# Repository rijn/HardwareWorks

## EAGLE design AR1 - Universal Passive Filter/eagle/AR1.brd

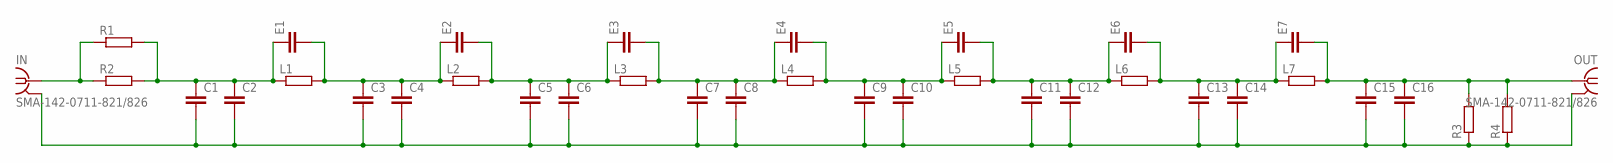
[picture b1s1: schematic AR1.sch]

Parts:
C1, C2, C3, C4, C5, C6, C7, C8, C9, C10, C11, C12, C13, C14, C15, C16: C; C0805
E1, E2, E3, E4, E5, E6, E7: C; C0805
IN: SMA-142-0711-821/826; J502-ND-142-0711-821/826
L1, L2, L3, L4, L5, L6, L7: R; R0805
OUT: SMA-142-0711-821/826; J502-ND-142-0711-821/826
R1, R2, R3, R4: R; R0805

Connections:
GND: C1.2, C2.2, C3.2, C4.2, C5.2, C6.2, C7.2, C8.2, C9.2, C10.2, C11.2, C12.2, C13.2, C14.2, C15.2, C16.2, IN.G@1 (2), IN.G@2 (2), IN.G@3 (2), IN.G@4 (2), OUT.G@1 (2), OUT.G@2 (2), OUT.G@3 (2), OUT.G@4 (2), R3.1, R4.1
unnamed: C1.1, C2.1, E1.1, L1.1, R1.2, R2.2
unnamed: IN.1, R1.1, R2.1
unnamed: C15.1, C16.1, E7.2, L7.2, OUT.1, R3.2, R4.2
unnamed: C3.1, C4.1, E1.2, E2.1, L1.2, L2.1
unnamed: C5.1, C6.1, E2.2, E3.1, L2.2, L3.1
unnamed: C7.1, C8.1, E3.2, E4.1, L3.2, L4.1
unnamed: C9.1, C10.1, E4.2, E5.1, L4.2, L5.1
unnamed: C11.1, C12.1, E5.2, E6.1, L5.2, L6.1
unnamed: C13.1, C14.1, E6.2, E7.1, L6.2, L7.1

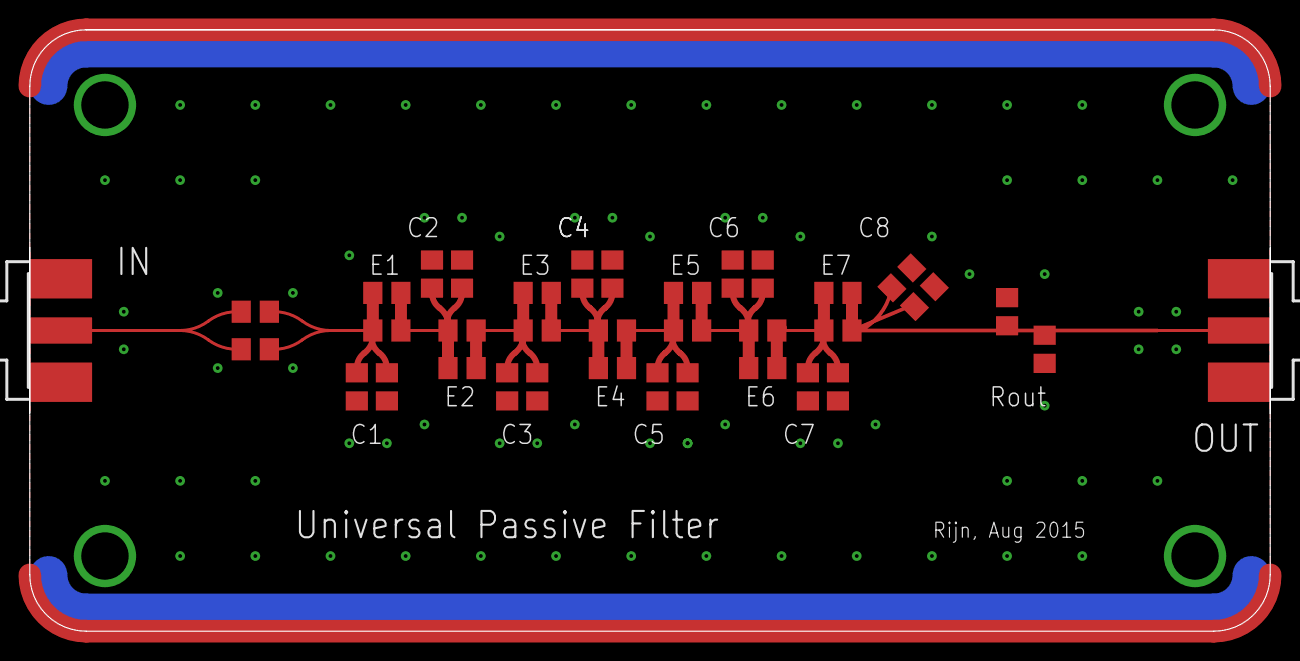
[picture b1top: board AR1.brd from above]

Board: 2 copper layers, 83.8 x 40.6 mm, 36 parts (0 on the bottom side), 10 nets.

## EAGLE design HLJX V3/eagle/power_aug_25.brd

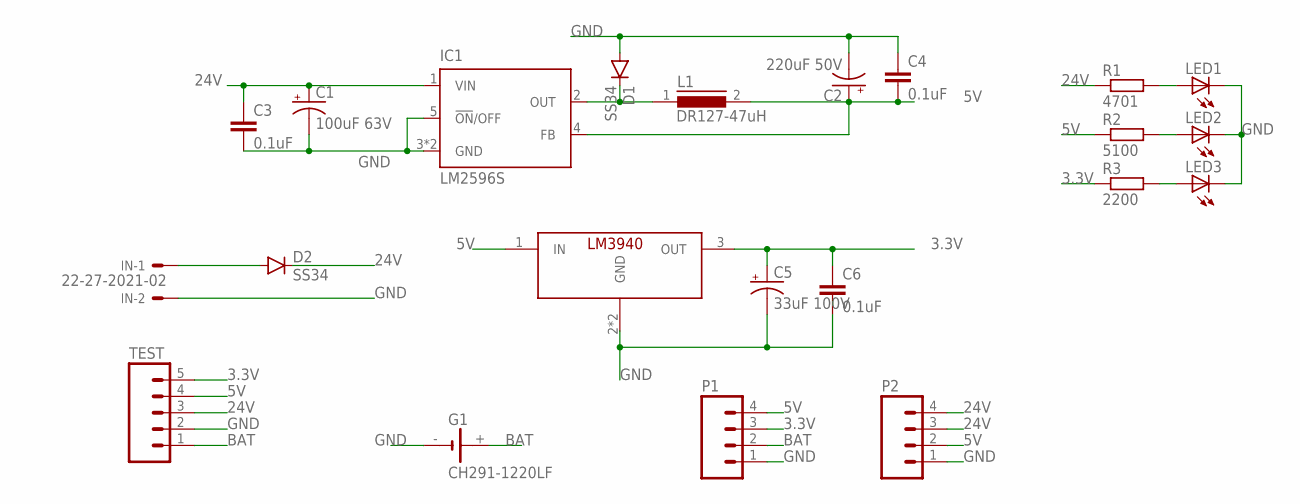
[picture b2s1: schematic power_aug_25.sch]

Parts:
C1: 100uF 63V; NIC_10X10.5_CAP
C2: 220uF 50V; NIC_10X10.5_CAP
C3, C4, C6: 0.1uF; 0603-CAP
C5: 33uF 100V; NIC_10X10.5_CAP
D1, D2: SS34; SMA-DIODE_ALT
G1: CH291-1220LF
IC1: LM2596S; TO263-5
IN: 22-27-2021-02; 6410-02
L1: DR127-47uH; DR127
LED1, LED2, LED3: LEDCHIPLED_0805; CHIPLED_0805
P1, P2: M04SMD2; 1X04-1MM-RA
R1: 4701; R0603
R2: 5100; R0603
R3: 2200; R0603
TEST: M05LOCK_LONGPADS; 1X05_LOCK_LONGPADS
U$1: LM3940; SOT223

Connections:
3.3V: C5.+, C6.1, P1.3, R3.1, TEST.5, U$1.3 (OUT)
5V: C2.+, C4.2, IC1.4 (FB), L1.2, P1.4, P2.2, R2.1, TEST.4, U$1.1 (IN)
24V: C1.+, C3.1, D2.C, IC1.1 (VIN), P2.3, P2.4, R1.1, TEST.3
BAT: G1.+, P1.2, TEST.1
GND: C1.-, C2.-, C3.2, C4.1, C5.-, C6.2, D1.A, G1.-, IC1.3 (GND), IC1.5 (!ON!/OFF), IC1.6 (GND), IN.2, LED1.C, LED2.C, LED3.C, P1.1, P2.1, TEST.2, U$1.2 (GND), U$1.4 (GND)
unnamed: D2.A, IN.1
unnamed: D1.C, IC1.2 (OUT), L1.1
unnamed: LED1.A, R1.2
unnamed: LED2.A, R2.2
unnamed: LED3.A, R3.2

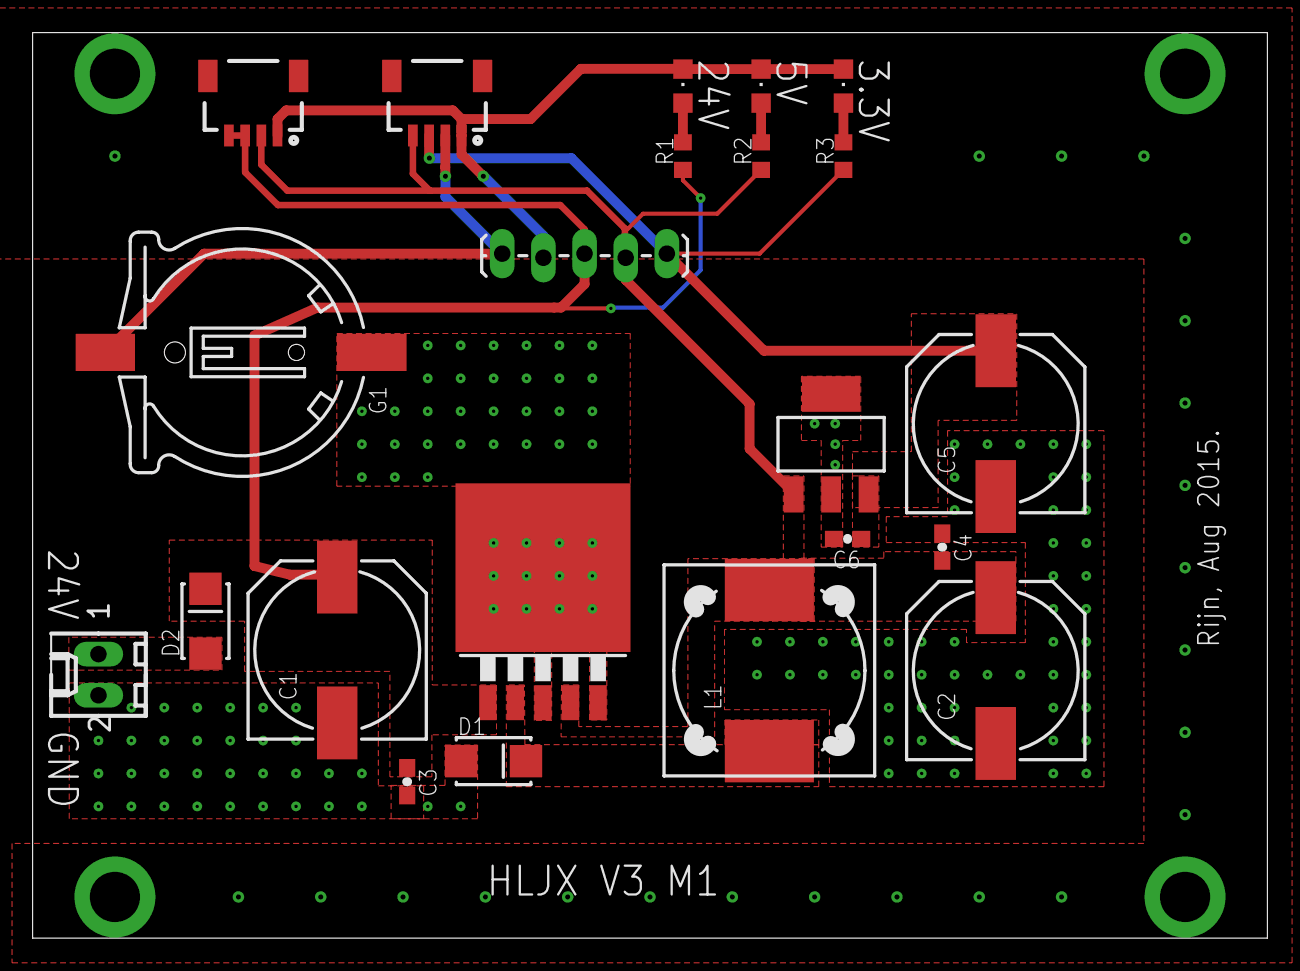
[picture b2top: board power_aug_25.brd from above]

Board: 2 copper layers, 76.2 x 55.9 mm, 22 parts (0 on the bottom side), 10 nets.

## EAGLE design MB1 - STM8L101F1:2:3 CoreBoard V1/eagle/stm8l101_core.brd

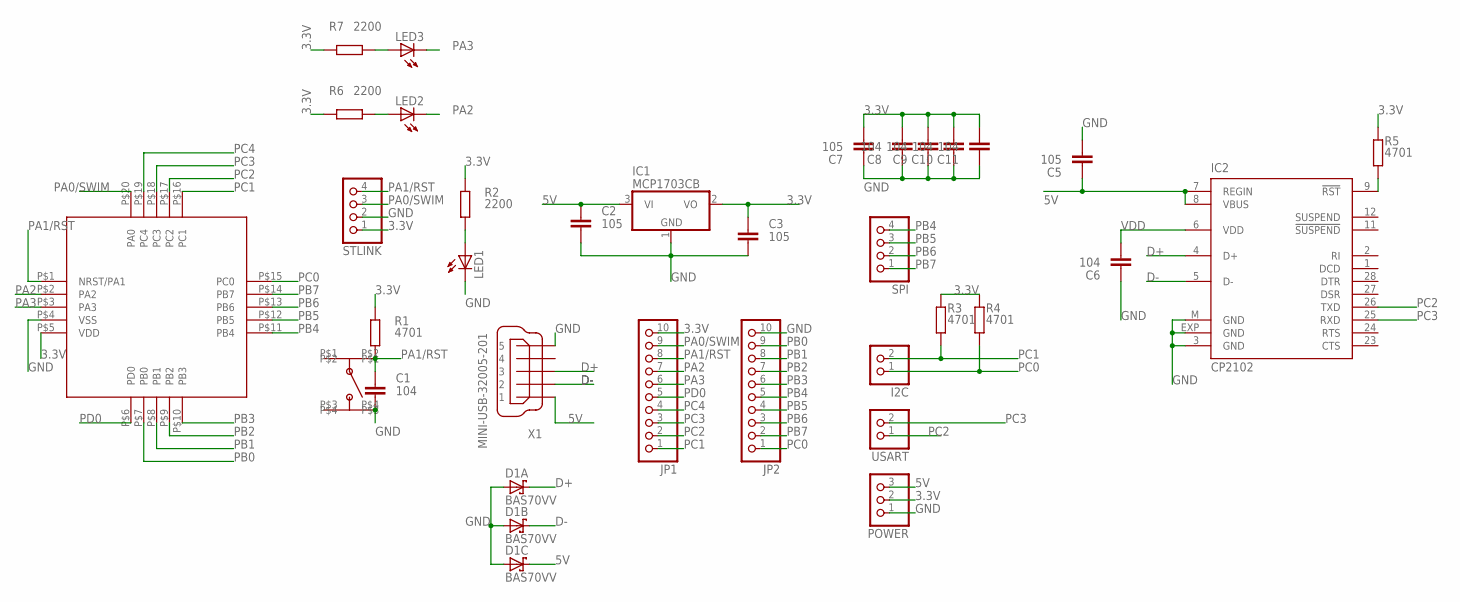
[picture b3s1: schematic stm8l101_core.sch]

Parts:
C1, C6, C8, C9, C10, C11: 104; C0603
C2, C3, C5, C7: 105; C0603
D1: BAS70VV; SOT666
I2C: PINHD-1X2; 1X02
IC1: MCP1703CB; SOT23
IC2: CP2102; MLP28
JP1, JP2: PINHD-1X10; 1X10
LED1, LED2, LED3: LED_ESML0603; LED_SML0603
POWER: PINHD-1X3; 1X03
R1, R3, R4, R5: 4701; R0603
R2, R6, R7: 2200; R0603
SPI: PINHD-1X4; 1X04
STLINK: PINHD-1X4; 1X04
U$1: STM8L101; UFQFPN20
U$2: KFC-A05; SWITCH-4X4
USART: PINHD-1X2; 1X02
X1: MINI-USB-32005-201; 32005-201

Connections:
3.3V: C3.1, C7.2, C8.2, C9.2, C10.2, C11.2, IC1.2 (VO), JP1.10, POWER.2, R1.1, R2.1, R3.1, R4.1, R5.1, R6.1, R7.1, STLINK.1, U$1.P$5 (VDD)
5V: C2.1, C5.1, D1.4 (C), IC1.3 (VI), IC2.7 (REGIN), IC2.8 (VBUS), POWER.3, X1.1
D+: D1.6 (C), IC2.4 (D+), X1.3
D-: D1.5 (C), IC2.5 (D-), X1.2
GND: C1.2, C2.2, C3.2, C5.2, C6.1, C7.1, C8.1, C9.1, C10.1, C11.1, D1.1 (A), D1.2 (A), D1.3 (A), IC1.1 (GND), IC2.3 (GND), IC2.EXP (GND), IC2.M (GND), JP2.10, LED1.C, POWER.1, STLINK.2, U$1.P$4 (VSS), U$2.P$4, X1.5
unnamed: IC2.9 (!RST), R5.2
unnamed: LED1.A, R2.2
unnamed: LED2.A, R6.2
unnamed: LED3.A, R7.2
PA0/SWIM: JP1.9, STLINK.3, U$1.P$20 (PA0)
PA1/RST: C1.1, JP1.8, R1.2, STLINK.4, U$1.P$1 (NRST/PA1), U$2.P$2
PA2: JP1.7, LED2.C, U$1.P$2 (PA2)
PA3: JP1.6, LED3.C, U$1.P$3 (PA3)
PB0: JP2.9, U$1.P$7 (PB0)
PB1: JP2.8, U$1.P$8 (PB1)
PB2: JP2.7, U$1.P$9 (PB2)
PB3: JP2.6, U$1.P$10 (PB3)
PB4: JP2.5, SPI.4, U$1.P$11 (PB4)
PB5: JP2.4, SPI.3, U$1.P$12 (PB5)
PB6: JP2.3, SPI.2, U$1.P$13 (PB6)
PB7: JP2.2, SPI.1, U$1.P$14 (PB7)
PC0: I2C.1, JP2.1, R4.2, U$1.P$15 (PC0)
PC1: I2C.2, JP1.1, R3.2, U$1.P$16 (PC1)
PC2: IC2.26 (TXD), JP1.2, U$1.P$17 (PC2), USART.1
PC3: IC2.25 (RXD), JP1.3, U$1.P$18 (PC3), USART.2
PC4: JP1.4, U$1.P$19 (PC4)
PD0: JP1.5, U$1.P$6 (PD0)
VDD: C6.2, IC2.6 (VDD)

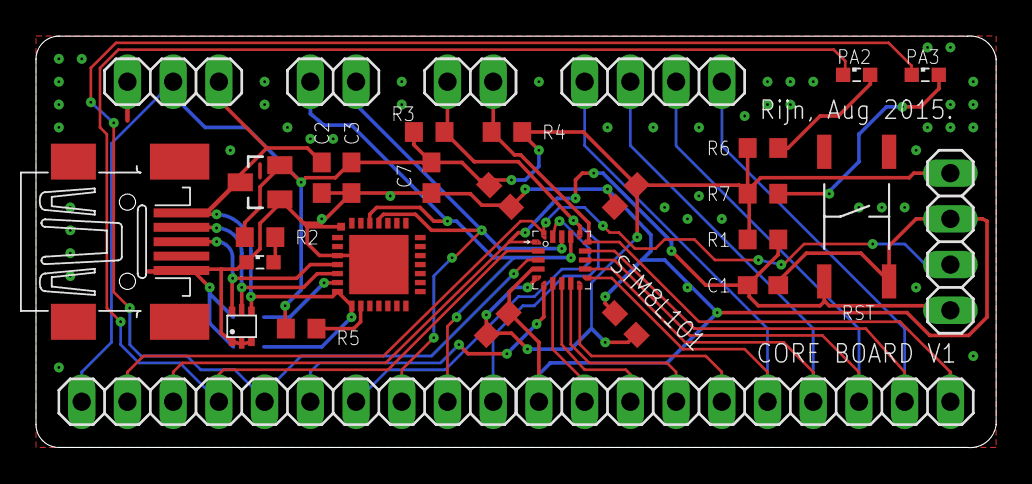
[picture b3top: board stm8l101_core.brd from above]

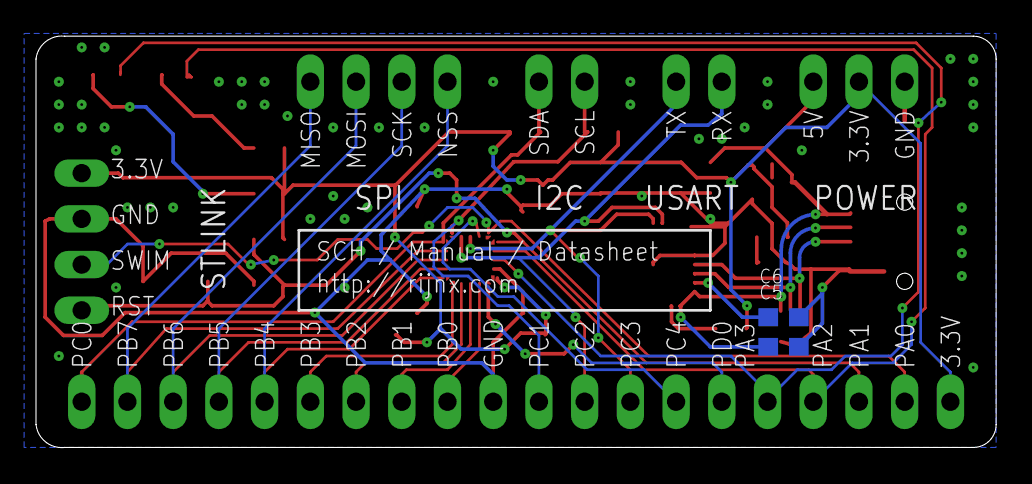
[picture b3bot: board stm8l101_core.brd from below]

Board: 2 copper layers, 53.3 x 22.9 mm, 33 parts (2 on the bottom side), 28 nets.

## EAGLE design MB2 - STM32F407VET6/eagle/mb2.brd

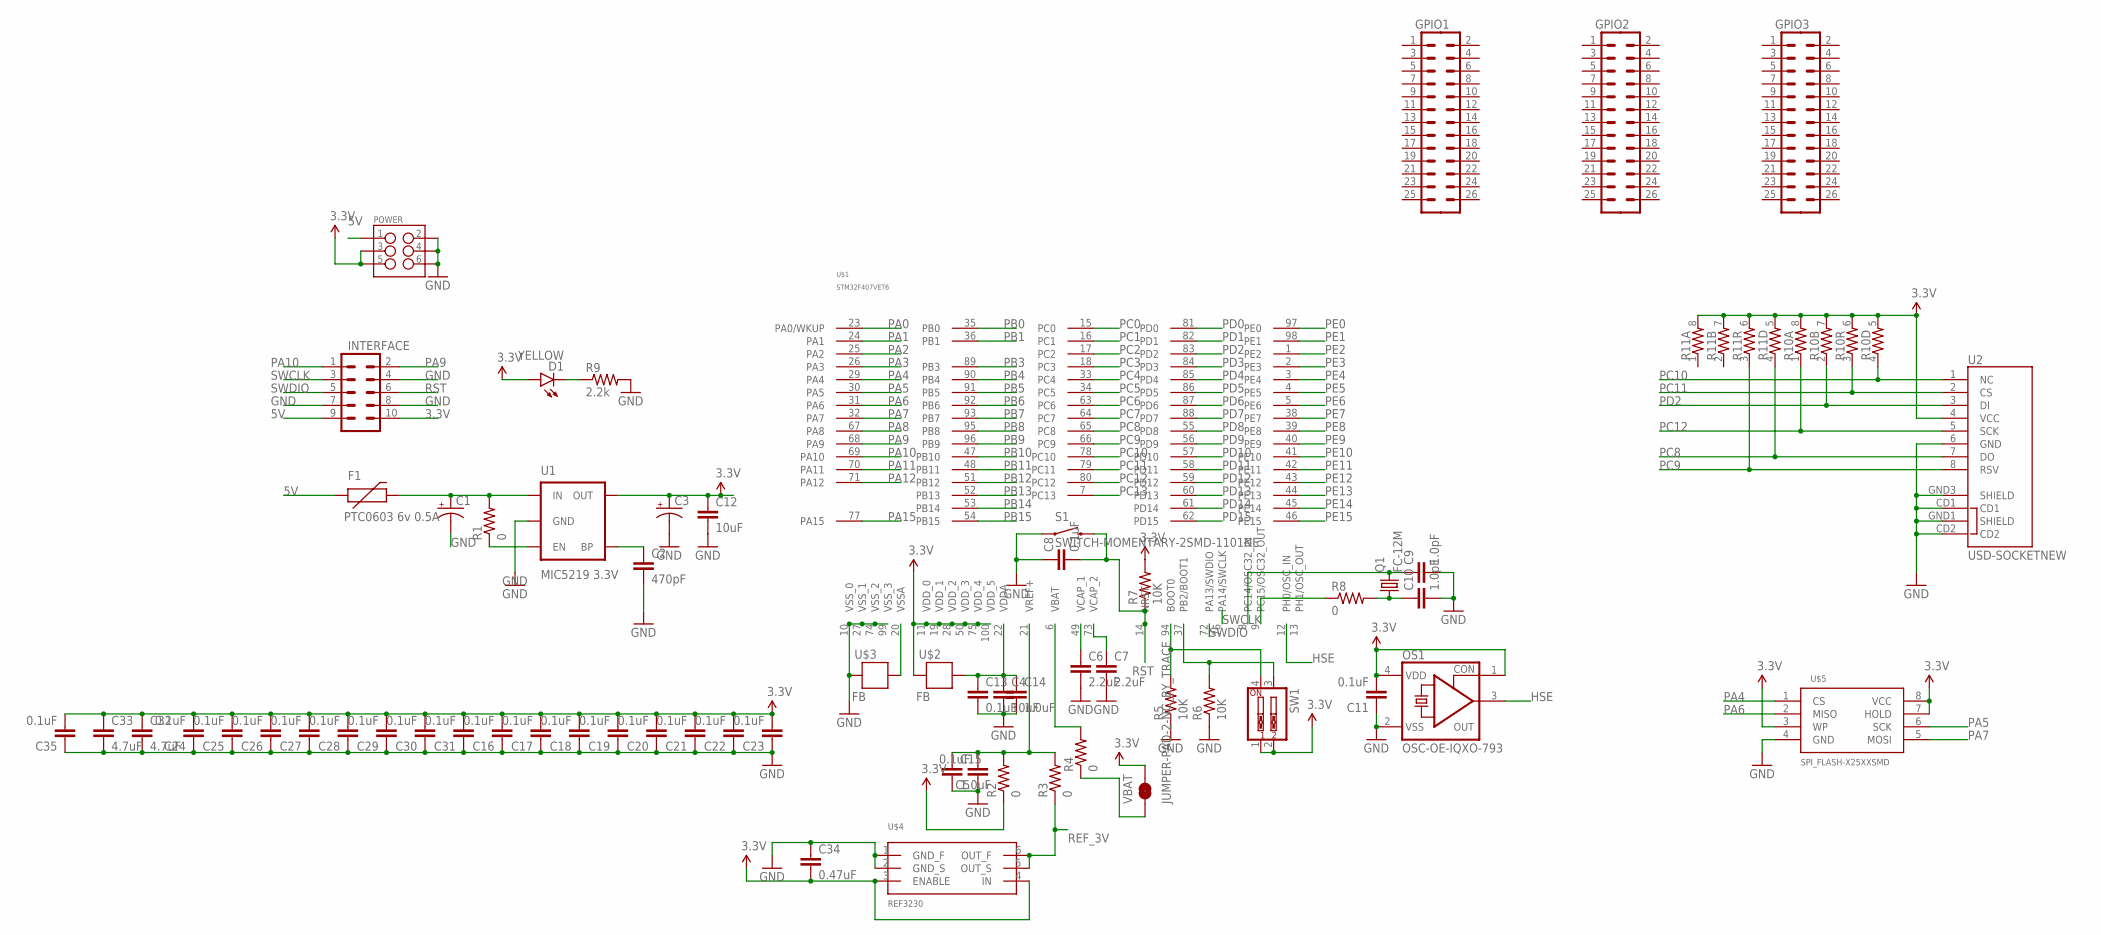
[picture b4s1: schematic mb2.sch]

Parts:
C1: CPOL-USB; PANASONIC_B
C2: 470pF; 0603-CAP
C3: CAP_POL1206; EIA3216
C4, C12: 10uF; 0603-CAP
C5, C8, C11, C13, C16, C17, C18, C19, C20, C21, C22, C23, C24, C25, C26, C27, C28, C29, C30, C31, C35: 0.1uF; 0603-CAP
C6, C7: 2.2uF; 0603-CAP
C9, C10: 1.0pF; 0603-CAP
C14, C15: 1.0uF; 0603-CAP
C32, C33: 4.7uF; 0603-CAP
C34: 0.47uF; 0603-CAP
D1: YELLOW; LED-1206
F1: PTC0603 6v 0.5A; 0603
GPIO1, GPIO2, GPIO3: M13X22X13; 2X13
INTERFACE: M05X2RA; 2X5-RA
OS1: OSC-OE-IQXO-793; 2.5X2-4-PAD
POWER: M03X22X3_SILK_MALE_PTH; 2X3
Q1: FC-12M
R1, R2, R3, R4, R8: 0; 0603
R5, R6, R7: 10K; 0603-RES
R9: 2.2k; 0603-RES
R10, R11: RESISTOR-ARRAY0603-ARV; 0603-ARV
S1: SWITCH-MOMENTARY-2SMD-1101NE; TACTILE-SWITCH-1101NE
SW1: SW_DIP-2-SMT-HALFSIZE; DIPSWITCH-02-50MIL
U1: MIC5219 3.3V; SOT23-5
U2: USD-SOCKETNEW; MICRO-SD-SOCKET-PP
U$1: STM32F407VET6; LQFP-100
U$2, U$3: FB; 0603
U$4: REF3230; SOT23-6
U$5: SPI_FLASH-X25XXSMD; SO08
VBAT: JUMPER-PAD-2-NC_BY_TRACE; PAD-JUMPER-2-NC_BY_TRACE_YES_SILK

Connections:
3.3V: C3.A (+), C11.2, C12.1, C16.2, C17.2, C18.2, C19.2, C20.2, C21.2, C22.2, C23.2, C24.2, C25.2, C26.2, C27.2, C28.2, C29.2, C30.2, C31.2, C32.1, C33.1, C34.2, C35.2, D1.A, INTERFACE.10, OS1.1 (CON), OS1.4 (VDD), POWER.3, POWER.5, R2.1, R7.2, R10.5 (2), R10.6 (2), R10.7 (2), R10.8 (2), R11.5 (2), R11.6 (2), R11.7 (2), R11.8 (2), SW1.1, SW1.2, U1.5 (OUT), U2.4 (VCC), U$1.11 (VDD_0), U$1.19 (VDD_1), U$1.28 (VDD_2), U$1.50 (VDD_3), U$1.75 (VDD_4), U$1.100 (VDD_5), U$2.2, U$4.3 (ENABLE), U$4.4 (IN), U$5.3 (WP), U$5.7 (HOLD), U$5.8 (VCC), VBAT.2
5V: F1.1, INTERFACE.9, POWER.1
GND: C1.-, C2.2, C3.C (-), C4.2, C5.1, C6.2, C7.2, C8.1, C9.2, C10.2, C11.1, C12.2, C13.2, C14.2, C15.2, C16.1, C17.1, C18.1, C19.1, C20.1, C21.1, C22.1, C23.1, C24.1, C25.1, C26.1, C27.1, C28.1, C29.1, C30.1, C31.1, C32.2, C33.2, C34.1, C35.1, INTERFACE.4, INTERFACE.7, INTERFACE.8, OS1.2 (VSS), POWER.2, POWER.4, POWER.6, R5.1, R6.1, R9.2, S1.1, U1.2 (GND), U2.6 (GND), U2.CD1, U2.CD2, U2.GND1 (SHIELD), U2.GND3 (SHIELD), U$1.10 (VSS_0), U$1.27 (VSS_1), U$1.74 (VSS_2), U$1.99 (VSS_3), U$3.2, U$4.1 (GND_F), U$4.2 (GND_S), U$5.4 (GND)
HSE: OS1.3 (OUT), U$1.12 (PH0/OSC_IN)
unnamed: C1.+, F1.2, R1.2, U1.1 (IN)
unnamed: R1.1, U1.3 (EN)
unnamed: C2.1, U1.4 (BP)
unnamed: U$1.20 (VSSA), U$3.1
unnamed: R4.1, VBAT.1
unnamed: C4.1, C13.1, C14.1, U$1.22 (VDDA), U$2.1
unnamed: C5.2, C15.1, R2.2, R3.2, U$1.21 (VREF+)
unnamed: C6.1, U$1.49 (VCAP_1)
unnamed: C7.1, U$1.73 (VCAP_2)
unnamed: R4.2, U$1.6 (VBAT)
unnamed: R5.2, SW1.4, U$1.94 (BOOT0)
unnamed: R6.2, SW1.3, U$1.37 (PB2/BOOT1)
unnamed: R8.1, U$1.9 (PC15/OSC32_OUT)
unnamed: C10.1, Q1.1, R8.2
unnamed: C9.1, Q1.2, U$1.8 (PC14/OSC32_IN)
unnamed: D1.C, R9.1
PA0: U$1.23 (PA0/WKUP)
PA1: U$1.24 (PA1)
PA2: U$1.25 (PA2)
PA3: U$1.26 (PA3)
PA4: U$1.29 (PA4), U$5.1 (CS)
PA5: U$1.30 (PA5), U$5.6 (SCK)
PA6: U$1.31 (PA6), U$5.2 (MISO)
PA7: U$1.32 (PA7), U$5.5 (MOSI)
PA8: U$1.67 (PA8)
PA9: INTERFACE.2, U$1.68 (PA9)
PA10: INTERFACE.1, U$1.69 (PA10)
PA11: U$1.70 (PA11)
PA12: U$1.71 (PA12)
PA15: U$1.77 (PA15)
PB0: U$1.35 (PB0)
PB1: U$1.36 (PB1)
PB3: U$1.89 (PB3)
PB4: U$1.90 (PB4)
PB5: U$1.91 (PB5)
PB6: U$1.92 (PB6)
PB7: U$1.93 (PB7)
PB8: U$1.95 (PB8)
PB9: U$1.96 (PB9)
PB10: U$1.47 (PB10)
PB11: U$1.48 (PB11)
PB12: U$1.51 (PB12)
PB13: U$1.52 (PB13)
PB14: U$1.53 (PB14)
PB15: U$1.54 (PB15)
PC0: U$1.15 (PC0)
PC1: U$1.16 (PC1)
PC2: U$1.17 (PC2)
PC3: U$1.18 (PC3)
PC4: U$1.33 (PC4)
PC5: U$1.34 (PC5)
PC6: U$1.63 (PC6)
PC7: U$1.64 (PC7)
PC8: R11.4 (1), U2.7 (DO), U$1.65 (PC8)
PC9: R11.3 (1), U2.8 (RSV), U$1.66 (PC9)
PC10: R10.4 (1), U2.1 (NC), U$1.78 (PC10)
PC11: R10.3 (1), U2.2 (CS), U$1.79 (PC11)
PC12: R10.1, U2.5 (SCK), U$1.80 (PC12)
PC13: U$1.7 (PC13)
PD0: U$1.81 (PD0)
PD1: U$1.82 (PD1)
PD2: R10.2 (1), U2.3 (DI), U$1.83 (PD2)
PD3: U$1.84 (PD3)
PD4: U$1.85 (PD4)
PD5: U$1.86 (PD5)
PD6: U$1.87 (PD6)
PD7: U$1.88 (PD7)
PD8: U$1.55 (PD8)
PD9: U$1.56 (PD9)
PD10: U$1.57 (PD10)
PD11: U$1.58 (PD11)
PD12: U$1.59 (PD12)
PD13: U$1.60 (PD13)
PD14: U$1.61 (PD14)
PD15: U$1.62 (PD15)
PE0: U$1.97 (PE0)
PE1: U$1.98 (PE1)
PE2: U$1.1 (PE2)
PE3: U$1.2 (PE3)
PE4: U$1.3 (PE4)
PE5: U$1.4 (PE5)
PE6: U$1.5 (PE6)
PE7: U$1.38 (PE7)
PE8: U$1.39 (PE8)
PE9: U$1.40 (PE9)
PE10: U$1.41 (PE10)
PE11: U$1.42 (PE11)
PE12: U$1.43 (PE12)
PE13: U$1.44 (PE13)
PE14: U$1.45 (PE14)
PE15: U$1.46 (PE15)
REF_3V: R3.1, U$4.5 (OUT_S), U$4.6 (OUT_F)
RST: C8.2, INTERFACE.6, R7.1, S1.2, U$1.14 (NRST)
SWCLK: INTERFACE.3, U$1.76 (PA14/SWCLK)
SWDIO: INTERFACE.5, U$1.72 (PA13/SWDIO)

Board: 4 copper layers, 65 parts (27 on the bottom side), 36 nets, no tracks yet.

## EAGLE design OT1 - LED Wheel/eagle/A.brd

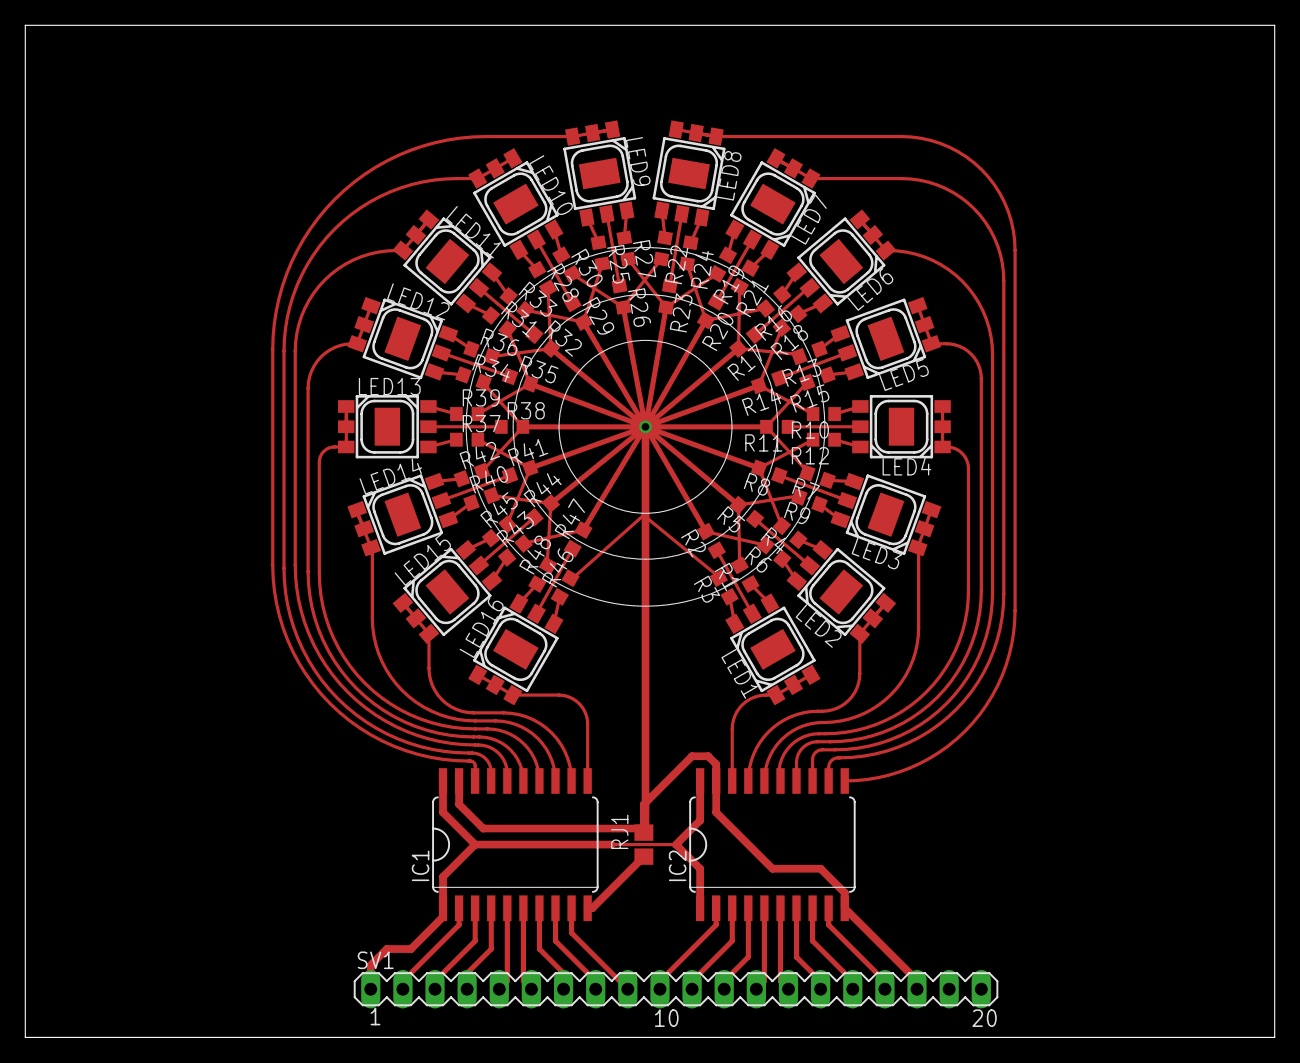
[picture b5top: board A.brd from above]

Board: 2 copper layers, 98.8 x 80.0 mm, 68 parts (0 on the bottom side), 82 nets.

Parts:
IC1, IC2: 74LS245DW; SO20W
LED1, LED2, LED3, LED4, LED5, LED6, LED7, LED8, LED9, LED10, LED11, LED12, LED13, LED14, LED15, LED16: LP2C63-ST-RGB-SR0
R1, R2, R3, R4, R5, R6, R7, R8, R9, R10, R11, R12, R13, R14, R15, R16, R17, R18, R19, R20, R21, R22, R23, R24, R25, R26, R27, R28, R29, R30, R31, R32, R33, R34, R35, R36, R37, R38, R39, R40, R41, R42, R43, R44, R45, R46, R47, R48: R0603
RJ1: R0805
SV1: MA20-1

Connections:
GND: IC1.10, IC1.19, IC2.10, IC2.19, R1.2, R2.2, R3.2, R4.2, R5.2, R6.2, R7.2, R8.2, R9.2, R10.2, R11.2, R12.2, R13.2, R14.2, R15.2, R16.2, R17.2, R18.2, R19.2, R20.2, R21.2, R22.2, R23.2, R24.2, R25.2, R26.2, R27.2, R28.2, R29.2, R30.2, R31.2, R32.2, R33.2, R34.2, R35.2, R36.2, R37.2, R38.2, R39.2, R40.2, R41.2, R42.2, R43.2, R44.2, R45.2, R46.2, R47.2, R48.2, RJ1.1, RJ1.2, SV1.18
unnamed: LED1.4, R1.1
unnamed: LED1.5, R2.1
unnamed: LED1.6, R3.1
unnamed: LED2.4, R4.1
unnamed: LED2.5, R5.1
unnamed: LED2.6, R6.1
unnamed: LED3.4, R7.1
unnamed: LED3.5, R8.1
unnamed: LED3.6, R9.1
unnamed: LED4.4, R10.1
unnamed: LED4.5, R11.1
unnamed: LED4.6, R12.1
unnamed: LED5.4, R13.1
unnamed: LED5.5, R14.1
unnamed: LED5.6, R15.1
unnamed: LED6.4, R16.1
unnamed: LED6.5, R17.1
unnamed: LED6.6, R18.1
unnamed: LED7.4, R19.1
unnamed: LED7.5, R20.1
unnamed: LED7.6, R21.1
unnamed: LED8.4, R22.1
unnamed: LED8.5, R23.1
unnamed: LED8.6, R24.1
unnamed: LED9.4, R25.1
unnamed: LED9.5, R26.1
unnamed: LED9.6, R27.1
unnamed: LED10.4, R28.1
unnamed: LED10.5, R29.1
unnamed: LED10.6, R30.1
unnamed: LED11.4, R31.1
unnamed: LED11.5, R32.1
unnamed: LED11.6, R33.1
unnamed: LED12.4, R34.1
unnamed: LED12.5, R35.1
unnamed: LED12.6, R36.1
unnamed: LED13.4, R37.1
unnamed: LED13.5, R38.1
unnamed: LED13.6, R39.1
unnamed: LED14.4, R40.1
unnamed: LED14.5, R41.1
unnamed: LED14.6, R42.1
unnamed: LED15.4, R43.1
unnamed: LED15.5, R44.1
unnamed: LED15.6, R45.1
unnamed: LED16.4, R46.1
unnamed: LED16.5, R47.1
unnamed: LED16.6, R48.1
O1: IC2.18, LED1.1, LED1.2, LED1.3
O2: IC2.17, LED2.1, LED2.2, LED2.3
O3: IC2.16, LED3.1, LED3.2, LED3.3
O4: IC2.15, LED4.1, LED4.2, LED4.3
O5: IC2.14, LED5.1, LED5.2, LED5.3
O6: IC2.13, LED6.1, LED6.2, LED6.3
O7: IC2.12, LED7.1, LED7.2, LED7.3
O8: IC2.11, LED8.1, LED8.2, LED8.3
O9: IC1.18, LED9.1, LED9.2, LED9.3
O10: IC1.17, LED10.1, LED10.2, LED10.3
O11: IC1.16, LED11.1, LED11.2, LED11.3
O12: IC1.15, LED12.1, LED12.2, LED12.3
O13: IC1.14, LED13.1, LED13.2, LED13.3
O14: IC1.13, LED14.1, LED14.2, LED14.3
O15: IC1.12, LED15.1, LED15.2, LED15.3
O16: IC1.11, LED16.1, LED16.2, LED16.3
P1: IC1.2, SV1.2
P2: IC1.3, SV1.3
P3: IC1.4, SV1.4
P4: IC1.5, SV1.5
P5: IC1.6, SV1.6
P6: IC1.7, SV1.7
P7: IC1.8, SV1.8
P8: IC1.9, SV1.9
P9: IC2.2, SV1.10
P10: IC2.3, SV1.11
P11: IC2.4, SV1.12
P12: IC2.5, SV1.13
P13: IC2.6, SV1.14
P14: IC2.7, SV1.15
P15: IC2.8, SV1.16
P16: IC2.9, SV1.17
VCC: IC1.1, IC1.20, IC2.1, IC2.20, SV1.1

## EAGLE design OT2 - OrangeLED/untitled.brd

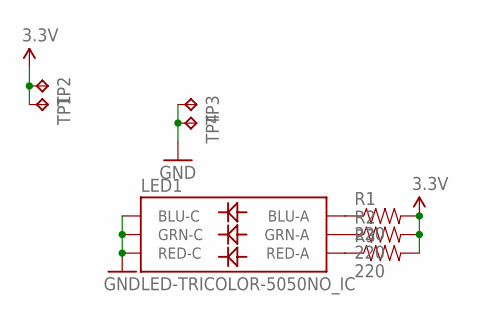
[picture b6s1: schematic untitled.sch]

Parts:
LED1: LED-TRICOLOR-5050NO_IC; LED-TRICOLOR-5050
R1, R2, R3: 220; 0603-RES
TP1, TP2, TP3, TP4: TPTP15SQ; TP15SQ

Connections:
3.3V: R1.2, R2.2, R3.2, TP1.TP, TP2.TP
GND: LED1.4 (BLU-C), LED1.5 (RED-C), LED1.6 (GRN-C), TP3.TP, TP4.TP
unnamed: LED1.3 (BLU-A), R1.1
unnamed: LED1.1 (GRN-A), R2.1
unnamed: LED1.2 (RED-A), R3.1

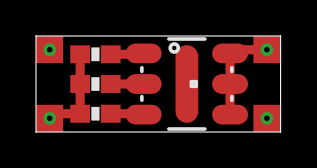
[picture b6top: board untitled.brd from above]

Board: 2 copper layers, 13.6 x 5.3 mm, 8 parts (0 on the bottom side), 5 nets.

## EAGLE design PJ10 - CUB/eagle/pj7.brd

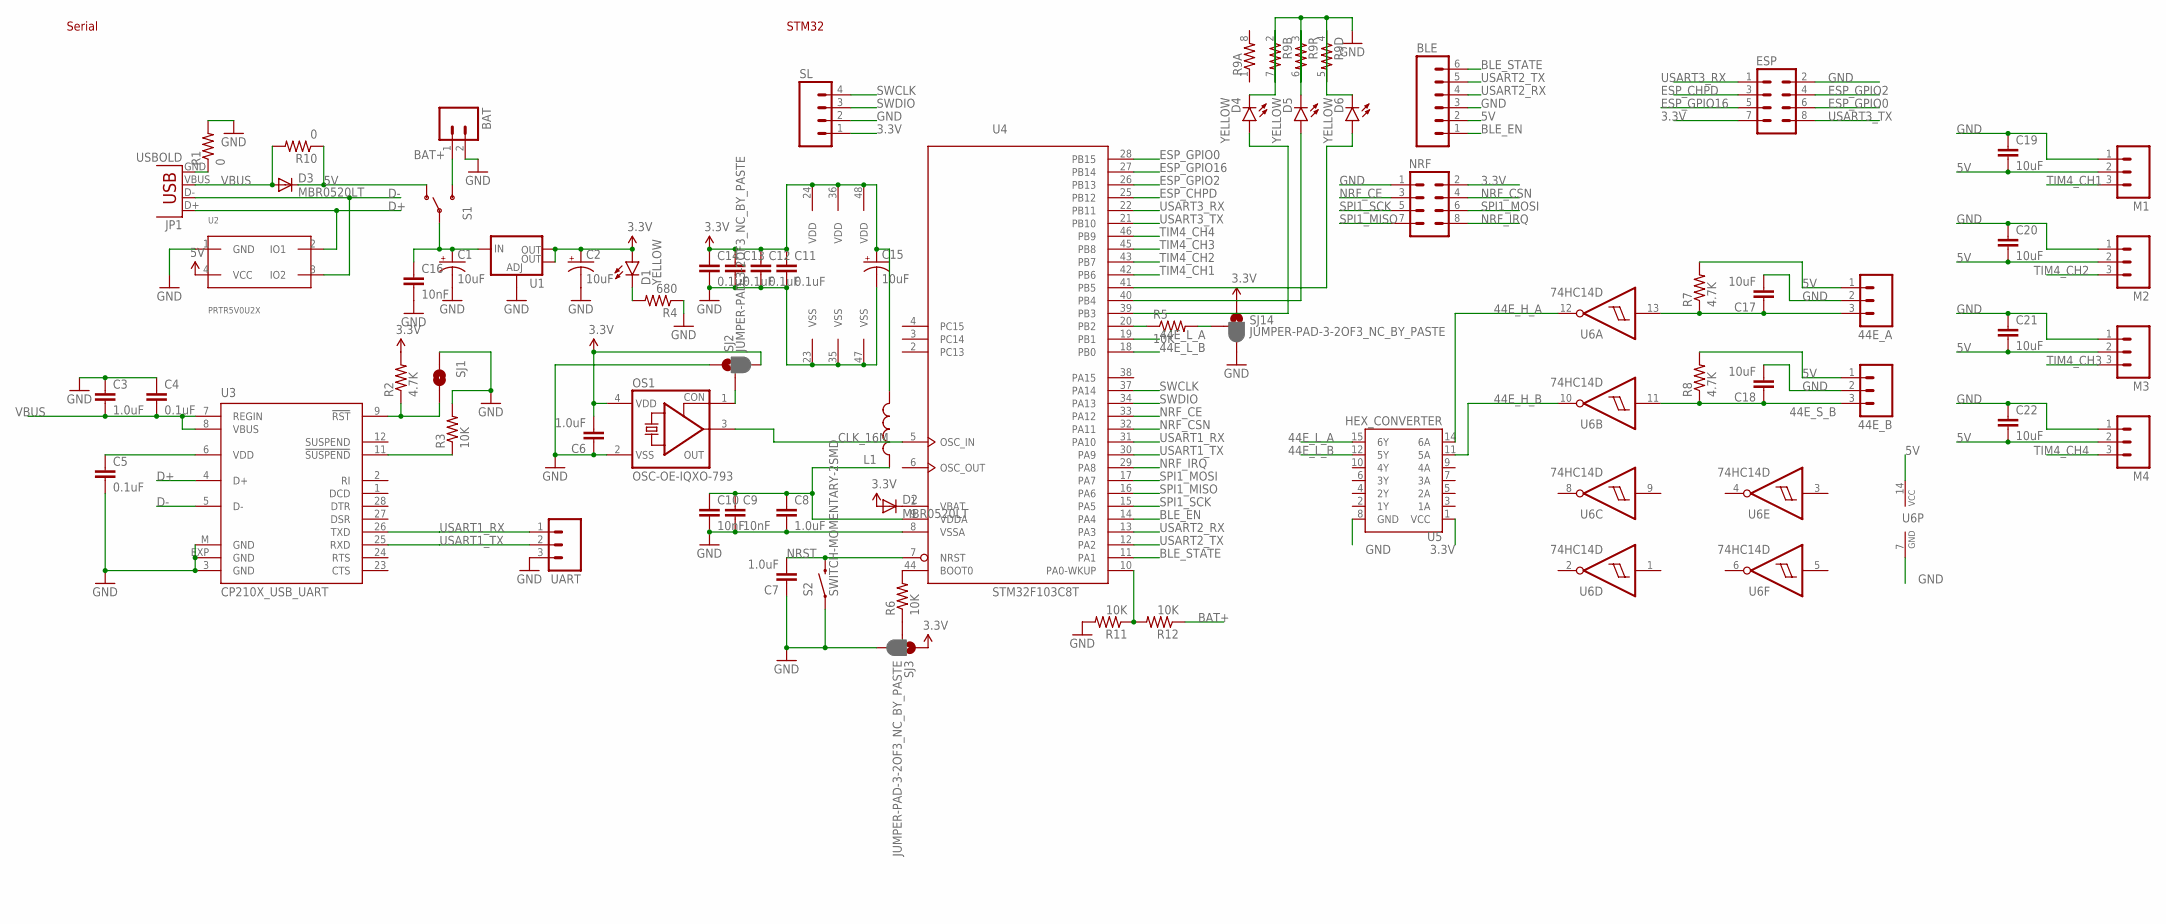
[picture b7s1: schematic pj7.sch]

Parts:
44E_A, 44E_B: M03LOCK; 1X03_LOCK
BAT: M02LOCK; 1X02_LOCK
BLE: M06LOCK; 1X06_LOCK
C1, C2, C15: 10uF; EIA3216
C3, C6, C7, C8: 1.0uF; 0603-CAP
C4, C5, C11, C12, C13, C14: 0.1uF; 0603-CAP
C9, C10, C16: 10nF; 0603-CAP
C17, C18, C19, C20, C21, C22: 10uF; 0603-CAP
D1, D4, D5, D6: YELLOW; LED-1206
D2, D3: MBR0520LT; SOD123
ESP: M04X2DIP; 2X4
JP1: USBOLD; USB-MINIB-OLD
L1: INDUCTOR0603; 0603
M1, M2, M3, M4: M03LOCK; 1X03_LOCK
NRF: M04X2DIP; 2X4
OS1: OSC-OE-IQXO-793; 2.5X2-4-PAD
R1, R10: 0; 0603
R2, R7, R8: 4.7K; 0603-RES
R3, R5, R6, R11, R12: 10K; 0603-RES
R4: 680; 0603-RES
R9: RESISTOR-ARRAY0603-ARV; 0603-ARV
S1: SWITCH-SPDTSMD; AYZ0202
S2: SWITCH-MOMENTARY-2SMD; TACTILE-SWITCH-SMD
SJ1: JUMPER-PAD-2-NOYES_SILK; PAD-JUMPER-2-NO_YES_SILK
SJ2, SJ3, SJ14: JUMPER-PAD-3-2OF3_NC_BY_PASTE; PAD-JUMPER-3-2OF3_NC_BY_PASTE_YES_SILK_FULL_BOX
SL: M04LOCK; 1X04_LOCK
U1: V_REG_LM1117SOT223; SOT223
U2: PRTR5V0U2X; SOT143
U3: CP210X_USB_UART; MLP28
U4: STM32F103C8T; LQFP48
U5: HEX_CONVERTER; SO016
U6: 74HC14D; SO14
UART: M03LOCK; 1X03_LOCK

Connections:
3.3V: C2.A (+), C6.2, C11.1, C12.1, C13.1, C14.1, C15.A (+), D1.A, D2.A, ESP.7, L1.2, NRF.2, OS1.4 (VDD), R2.2, SJ2.3, SJ3.1, SJ14.1, SL.1, U1.2 (OUT), U1.4 (OUT), U4.24 (VDD), U4.36 (VDD), U4.48 (VDD), U5.1 (VCC)
5V: 44E_A.1, 44E_B.1, BLE.2, C19.2, C20.2, C21.2, C22.2, D3.C, M1.2, M2.2, M3.2, M4.2, R7.2, R8.2, R10.1, S1.1 (O), U2.4 (VCC), U6.14 (VCC)
44E_H_A: U5.14 (6A), U6.12 (O)
44E_H_B: U5.11 (5A), U6.10 (O)
44E_L_A: U4.19 (PB1), U5.15 (6Y)
44E_L_B: U4.18 (PB0), U5.12 (5Y)
44E_S_B: 44E_B.3, C18.1, R8.1, U6.11 (I)
BAT+: BAT.1, R12.1, S1.3 (S)
BLE_EN: BLE.1, U4.14 (PA4)
BLE_STATE: BLE.6, U4.11 (PA1)
CLK_16M: OS1.3 (OUT), U4.5 (OSC_IN)
D+: JP1.D+, U2.2 (IO1), U3.4 (D+)
D-: JP1.D-, U2.3 (IO2), U3.5 (D-)
ESP_CHPD: ESP.3, U4.25 (PB12)
ESP_GPIO0: ESP.6, U4.28 (PB15)
ESP_GPIO2: ESP.4, U4.26 (PB13)
ESP_GPIO16: ESP.5, U4.27 (PB14)
GND: 44E_A.2, 44E_B.2, BAT.2, BLE.3, C1.C (-), C2.C (-), C3.1, C4.1, C5.2, C6.1, C7.1, C8.2, C9.2, C10.2, C11.2, C12.2, C13.2, C14.2, C15.C (-), C16.2, C17.2, C18.2, C19.1, C20.1, C21.1, C22.1, ESP.2, M1.1, M2.1, M3.1, M4.1, NRF.1, OS1.2 (VSS), R1.2, R3.2, R4.1, R9.5 (2), R9.6 (2), R9.7 (2), R11.2, S2.1, SJ1.2, SJ2.1, SJ3.3, SJ14.3, SL.2, U1.1 (ADJ), U2.1 (GND), U3.3 (GND), U3.EXP (GND), U3.M (GND), U4.8 (VSSA), U4.23 (VSS), U4.35 (VSS), U4.47 (VSS), U5.8 (GND), U6.7 (GND), UART.3
unnamed: JP1.GND, R1.1
unnamed: R3.1, U3.11 (!SUSPEND)
unnamed: D1.C, R4.2
unnamed: D2.C, U4.1 (VBAT)
unnamed: R11.1, R12.2, U4.10 (PA0-WKUP)
unnamed: C8.1, C9.1, C10.1, L1.1, U4.9 (VDDA)
unnamed: R6.2, U4.44 (BOOT0)
unnamed: D6.A, U4.41 (PB5)
unnamed: R6.1, SJ3.2
unnamed: R2.1, SJ1.1, U3.9 (!RST)
unnamed: OS1.1 (CON), SJ2.2
unnamed: D5.A, U4.40 (PB4)
unnamed: 44E_A.3, C17.1, R7.1, U6.13 (I)
unnamed: C5.1, U3.6 (VDD)
unnamed: D4.A, U4.39 (PB3)
unnamed: D4.C, R9.2 (1)
unnamed: D5.C, R9.3 (1)
unnamed: D6.C, R9.4 (1)
unnamed: C1.A (+), C16.1, S1.2, U1.3 (IN)
unnamed: R5.2, SJ14.2
NRF_CE: NRF.3, U4.33 (PA12)
NRF_CSN: NRF.4, U4.32 (PA11)
NRF_IRQ: NRF.8, U4.29 (PA8)
NRST: C7.2, S2.3 (2), U4.7 (NRST)
OURET: R5.1, U4.20 (PB2)
SPI1_MISO: NRF.7, U4.16 (PA6)
SPI1_MOSI: NRF.6, U4.17 (PA7)
SPI1_SCK: NRF.5, U4.15 (PA5)
SWCLK: SL.4, U4.37 (PA14)
SWDIO: SL.3, U4.34 (PA13)
TIM4_CH1: M1.3, U4.42 (PB6)
TIM4_CH2: M2.3, U4.43 (PB7)
TIM4_CH3: M3.3, U4.45 (PB8)
TIM4_CH4: M4.3, U4.46 (PB9)
USART1_RX: U3.26 (TXD), U4.31 (PA10), UART.1
USART1_TX: U3.25 (RXD), U4.30 (PA9), UART.2
USART2_RX: BLE.4, U4.13 (PA3)
USART2_TX: BLE.5, U4.12 (PA2)
USART3_RX: ESP.1, U4.22 (PB11)
USART3_TX: ESP.8, U4.21 (PB10)
VBUS: C3.2, C4.2, D3.A, JP1.VBUS, R10.2, U3.7 (REGIN), U3.8 (VBUS)

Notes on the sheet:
STM32
Serial

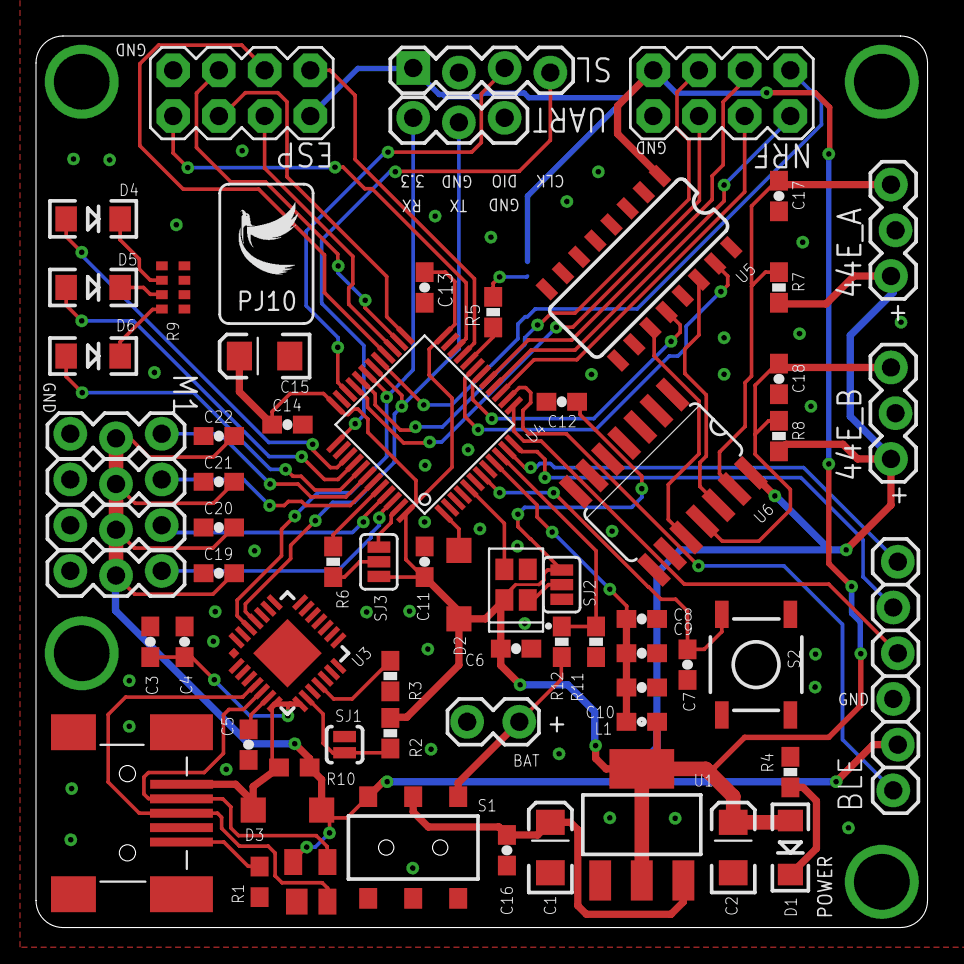
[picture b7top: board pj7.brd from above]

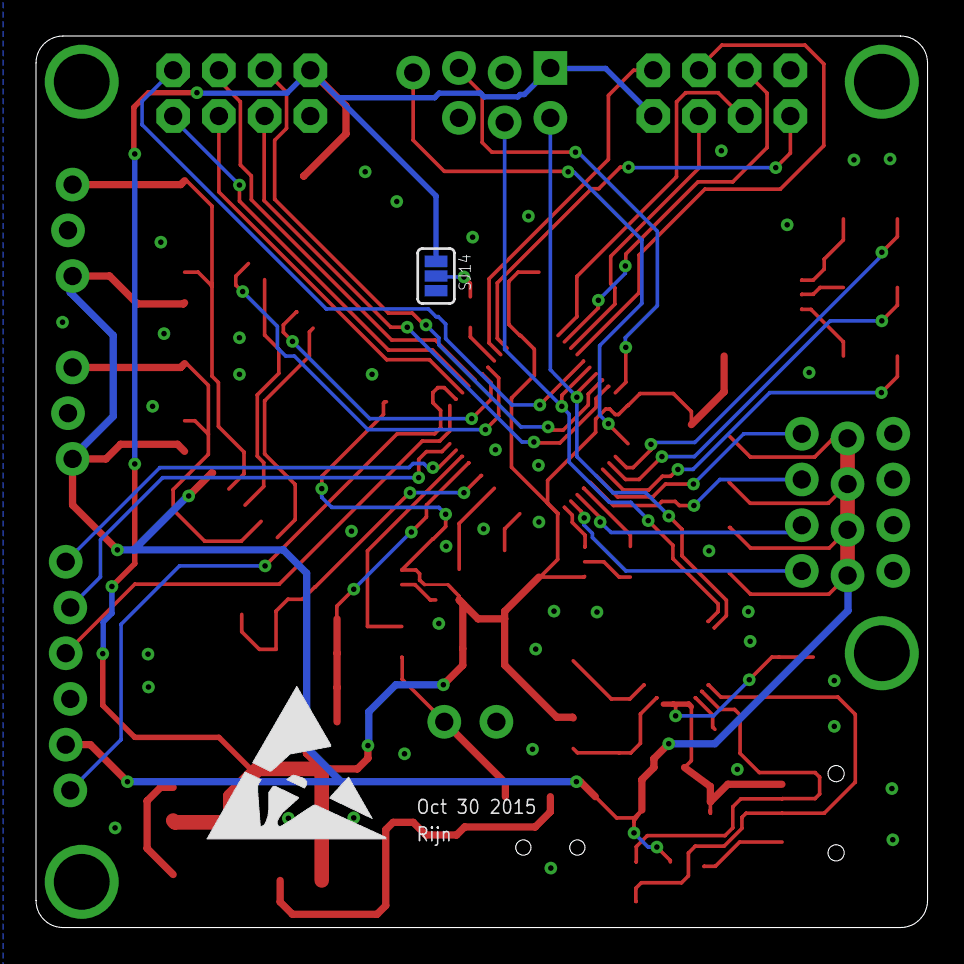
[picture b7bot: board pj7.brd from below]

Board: 2 copper layers, 49.5 x 49.5 mm, 69 parts (2 on the bottom side), 59 nets.

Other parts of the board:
U$1: LOGO
U$2: ESD_10.00

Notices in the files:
parts and their libraries:
SparkFun-Capacitors: Licensing: Creative Commons ShareAlike 4.0 International - https://creativecommons.org/licenses/by-sa/4.0
